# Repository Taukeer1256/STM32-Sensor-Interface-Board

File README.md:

# STM32 Sensor Interface Board

Schematic-level hardware design for an automotive-telematics sensor node — built as a portfolio project targeting hardware design (schematic capture, power/clock/reset design, CAN bus integration, PCB bring-up prep).

## Overview

A STM32F103C8Tx-based board with regulated power, CAN bus connectivity, a UART peripheral header, and an SWD programming interface. Designed in KiCad, schematic-first with PCB placement in progress.

> **Status:** Schematic complete and ERC-clean. PCB footprint placement done; routing in progress (X/53 nets routed).

## Block Diagram

```
5V in --> AMS1117-3.3 --> 3.3V rail --> STM32F103C8Tx --> CAN transceiver (SN65HVD230) --> CANH/CANL
                                              |--> USART1 header (J2)
                                              |--> SWD programming header (J1)
                                              |--> 8MHz HSE crystal
```

## Design Decisions

**Power stage — AMS1117-3.3**
Linear regulator chosen for prototype simplicity over a switching converter. Tradeoff: lower efficiency (acceptable at this current draw, not appropriate for a battery-powered final product — noted as a known limitation, not an oversight). 10µF bulk caps on input and output per datasheet's typical application circuit.

**Decoupling**
One 100nF ceramic cap per digital VDD pin (pins 24, 36, 48). VDDA (pin 9, analog supply) gets its own 100nF + 1µF pair, isolated per ST's datasheet guidance — analog supply noise directly affects ADC accuracy, so it's decoupled separately from the digital rails.

**Reset (NRST) — R1, 10kΩ pull-up**
STM32 has an internal NRST pull-up, so this is a deliberate redundant external pull-up rather than a requirement — added for reliability margin and to make the reset node easier to probe during bring-up.

**Boot mode (BOOT0) — R2, 10kΩ pull-down**
Pulled low for normal flash-boot operation. Pulling BOOT0 high on next reset would instead enter the STM32 system bootloader — relevant if a UART-based firmware recovery path is ever needed.

**Crystal — 8MHz HSE, C8/C9 load caps**
Load capacitor values calculated from the crystal datasheet's specified load capacitance using `C_load = (C1 × C2)/(C1 + C2) + C_stray`, with C_stray assumed ~3–5pF for board parasitics. Resulted in 18pF caps on both OSC pins.

**CAN transceiver — SN65HVD230**
3.3V-native transceiver chosen to match the STM32's I/O voltage directly (no level shifting needed). CANH/CANL broken out to the edge for external bus connection; 120Ω termination to be added only if this node is a physical bus endpoint.

**Debug/expansion**
- J1: 5-pin SWD header (SWDIO, SWCLK, NRST, 3V3, GND) for programming and debug
- J2: 3-pin USART1 header for peripheral/serial debug access

## Bill of Materials

| Ref | Part | Value | Notes |
|---|---|---|---|
| U1 | STM32F103C8Tx | — | 64KB flash, LQFP-48 |
| U2 | AMS1117-3.3 | — | Linear LDO |
| U3 | SN65HVD230 | — | 3.3V CAN transceiver |
| C1, C2 | Ceramic/Tantalum | 10µF | LDO input/output bulk caps |
| C3, C4, C5 | Ceramic | 100nF | VDD decoupling (pins 24, 36, 48) |
| C6 | Ceramic | 100nF | VDDA decoupling |
| C7 | Ceramic | 1µF | VDDA decoupling |
| C8, C9 | Ceramic | 18pF | Crystal load caps |
| R1 | Resistor | 10kΩ | NRST pull-up (redundant, reliability margin) |
| R2 | Resistor | 10kΩ | BOOT0 pull-down (normal boot) |
| Y1 | Crystal | 8MHz | HSE clock source |
| J1 | Header, 1x05 | — | SWD programming |
| J2 | Header, 1x03 | — | USART1 |

## Bring-Up Test Plan

| Test | Expected Result | Instrument |
|---|---|---|
| LDO output voltage | 3.3V ± 3% | DMM |
| VDD ripple (under load) | < 50mV pk-pk | Oscilloscope |
| NRST idle state | High (~3.3V) | DMM |
| BOOT0 idle state | Low (~0V) | DMM |
| HSE crystal oscillation | Clean 8MHz, stable amplitude | Oscilloscope |
| CAN idle bus state | ~2.5V on CANH/CANL (recessive) | DMM |
| SWD connectivity | Debugger enumerates STM32 | ST-Link / OpenOCD |

**Debug order if the board doesn't boot:** power rail → clock (crystal) → reset (NRST/BOOT0) → peripheral bus (CAN/UART). Check each stage before moving to the next rather than probing randomly.

## Tools

- KiCad 8.x — schematic capture and PCB layout
- Reference datasheets: STM32F103C8Tx, AMS1117-3.3, SN65HVD230

## Repo Structure

```
/schematic     -- .kicad_sch source + exported PDF
/pcb           -- .kicad_pcb source + exported PDF (routing in progress)
/docs          -- this README, BOM, bring-up test plan
```

## Known Limitations / Next Steps

- [ ] Finish PCB routing (13 nets outstanding as of last checkpoint)
- [ ] Add GNSS module footprint (planned, not yet implemented)
- [ ] Add 120Ω CAN termination resistor if this board is confirmed as a bus endpoint

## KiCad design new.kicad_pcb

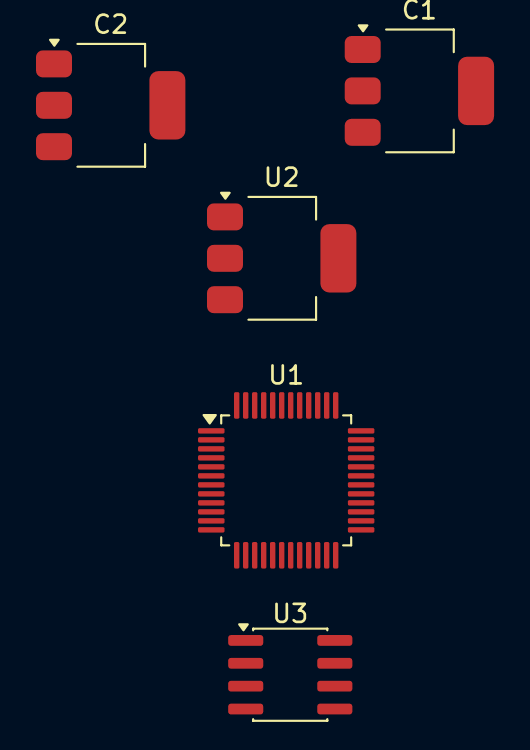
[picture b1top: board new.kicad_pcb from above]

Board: 2 copper layers, 5 parts (0 on the bottom side), 4 nets, no tracks yet.

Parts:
C1, C2: 10UF; SOT-223-3_TabPin2
U1: STM32F103C8Tx; LQFP-48_7x7mm_P0.5mm
U2: AMS1117-3.3; SOT-223-3_TabPin2
U3: SN65HVD230; SOIC-8_3.9x4.9mm_P1.27mm

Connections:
+3V3: U1.1 (VBAT), U3.3 (VCC)
/3V3: C2.1, U2.2 (VO)
/5V: C1.1, U2.3 (VI)
GND: C1.2, C2.2, U1.8 (VSSA), U1.23 (VSS), U1.35 (VSS), U1.47 (VSS), U2.1 (GND), U3.2 (GND)
